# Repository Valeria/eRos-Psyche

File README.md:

# eRos & Psyche
### **Open Source Dildo running on the ESP32 Platform**

V1.0 Attaches to a **ESP32-DevKitC-V4**, **check pinout to make sure it coincides**.

It's meant to drive three (or less) **3.3v motors, max 1A per PWM output**.
Use with Li-Po or Li-Ion **3.7v nominal voltage batteries**.

Connects to a **Blynk.io** server, which can be self-hosted, otherwise, use the free Blynk Cloud server or contact me for a spot on mine.

Mobile app can be recreated by scanning the following QR code on the Blynk phone app:

Hardware files are in the **eRos** directory, meant to be edited on **KiCad v5.0 or higher**.

Firmware files are in the **Psyche** directory, if you open the project on PlatformIO it should load all required Arduino libraries automatically, else, here's a list:

 - shaggydog/OneButton@^1.5.0
 - ayushsharma82/AsyncElegantOTA@^2.2.5
 - ottowinter/AsyncTCP-esphome@^1.2.1
 - ottowinter/ESPAsyncWebServer-esphome@^1.2.7
 - bblanchon/ArduinoJson@^6.17.3
 - s00500/ESPUI@^2.0.0
 - khoih.prog/Blynk_Async_ESP32_BT_WF@^1.2.1
 - adafruit/Adafruit BMP280 Library@^2.4.1
 - teckel12/NewPing@^1.9.1
 - gamegine/HCSR04 ultrasonic sensor@^2.0.2
 - adafruit/Adafruit_VL53L0X@^1.1.1

Firmware.bin must be built with the **huge_app.csv** partition scheme.

Have fun!

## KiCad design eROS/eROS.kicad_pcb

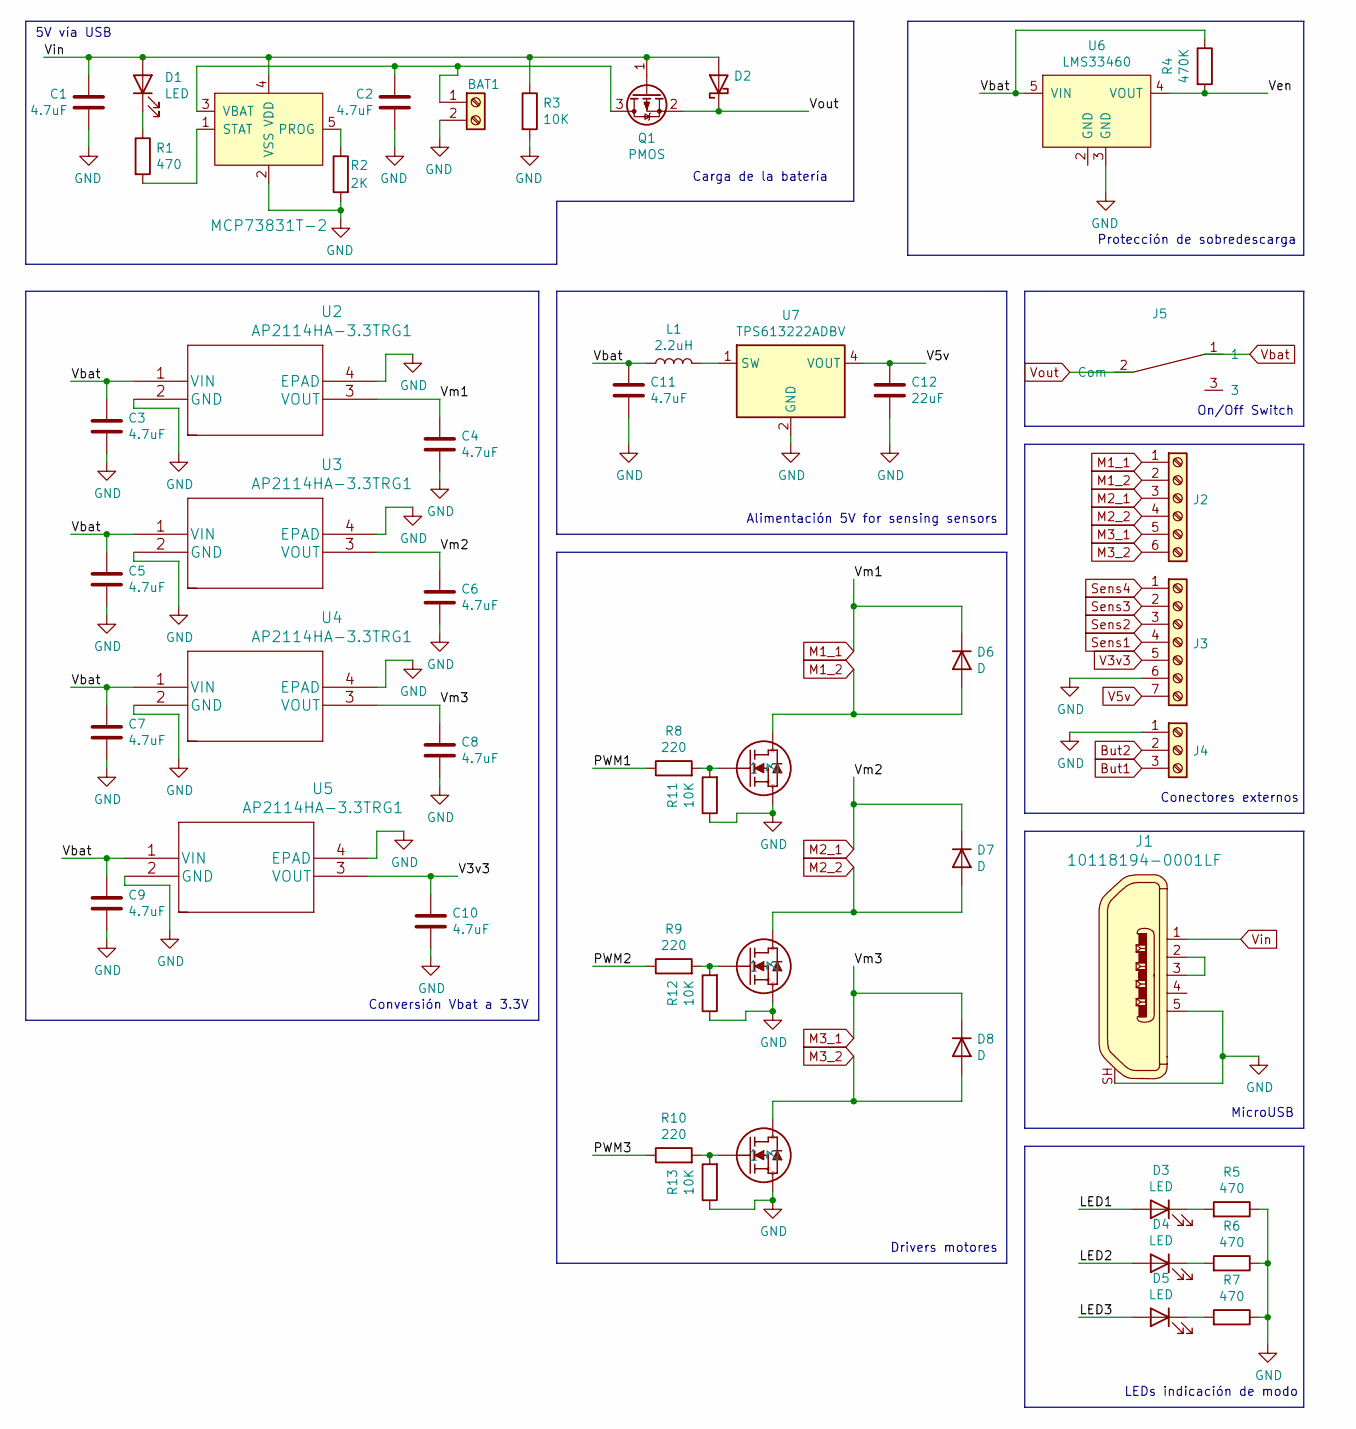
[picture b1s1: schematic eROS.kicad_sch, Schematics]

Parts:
BAT1: Screw_Terminal_01x02; JST_XH_B2B-XH-A_1x02_P2.50mm_Vertical
C1, C2, C3, C4, C5, C6, C7, C8, C9, C10, C11: 4.7uF; C_0805_2012Metric_Pad1.18x1.45mm_HandSolder
C12: 22uF; C_0805_2012Metric_Pad1.18x1.45mm_HandSolder
D1, D3, D4, D5: LED; LED_0805_2012Metric_Pad1.15x1.40mm_HandSolder
D2: D_Schottky; Nexperia_CFP3_SOD-123W_Handsolder
D6, D7, D8: D; Nexperia_CFP3_SOD-123W_Handsolder
J1: 10118194-0001LF; USB_Micro_B_Female_10118194-0001LF_HandSolder; MPN 10118194-0001LF; Digi-Key_PN 609-4618-1-ND
J2: Screw_Terminal_01x06; JST_XH_B6B-XH-A_1x06_P2.50mm_Vertical
J3: Screw_Terminal_01x07; PinHeader_1x07_P2.00mm_Horizontal
J4: Screw_Terminal_01x03; JST_XH_B3B-XH-A_1x03_P2.50mm_Vertical
J5: MiniSlideSwitch; JST_XH_B2B-XH-A_1x02_P2.50mm_Vertical
L1: 2.2uH; L_1008_2520Metric_Pad1.43x2.20mm_HandSolder
MOSFET1, MOSFET2, MOSFET3: IRLML6246TRPBF; SOT-23_Handsoldering
Q1: PMOS; SOT-23_Handsoldering
R1, R5, R6, R7: 470; R_0805_2012Metric_Pad1.20x1.40mm_HandSolder
R2: 2K; R_0805_2012Metric_Pad1.20x1.40mm_HandSolder
R3, R11, R12, R13: 10K; R_0805_2012Metric_Pad1.20x1.40mm_HandSolder
R4: 470K; R_0805_2012Metric_Pad1.20x1.40mm_HandSolder
R8, R9, R10: 220; R_0805_2012Metric_Pad1.20x1.40mm_HandSolder
U1: MCP73831T-2; SOT-23-5_HandSoldering; MPN MCP73831T-2DCI/OT; Digi-Key_PN MCP73831T-2DCI/OTCT-ND
U2, U3, U4, U5: AP2114HA-3.3TRG1; SOT-223-3_TabPin2
U6: LMS33460; SOT-353_SC-70-5_Handsoldering; mpn LMS33460
U7: TPS613222ADBV; SOT-23-5_HandSoldering

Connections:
/LED1: D3.2 (A)
/LED2: D4.2 (A)
/LED3: D5.2 (A)
/PWM1: R8.1
/PWM2: R9.1
/PWM3: R10.1
/Ven: R4.2, U6.4 (VOUT)
But1: J4.3
But2: J4.2
GND: BAT1.2, C1.2, C2.2, C3.2, C4.2, C5.2, C6.2, C7.2, C8.2, C9.2, C10.2, C11.2, C12.2, J1.5, J1.SH, J3.6, J4.1, MOSFET1.2, MOSFET2.2, MOSFET3.2, R2.2, R3.2, R5.1, R6.1, R7.1, R11.1, R12.1, R13.1, U1.2 (VSS), U2.2 (GND), U2.4 (EPAD), U3.2 (GND), U3.4 (EPAD), U4.2 (GND), U4.4 (EPAD), U5.2 (GND), U5.4 (EPAD), U6.3 (GND), U7.2 (GND)
M1_1: C4.1, D6.1 (K), J2.1, U2.3 (VOUT)
M1_2: D6.2 (A), J2.2, MOSFET1.3
M2_1: C6.1, D7.1 (K), J2.3, U3.3 (VOUT)
M2_2: D7.2 (A), J2.4, MOSFET2.3
M3_1: C8.1, D8.1 (K), J2.5, U4.3 (VOUT)
M3_2: D8.2 (A), J2.6, MOSFET3.3
unnamed: BAT1.1, C2.1, Q1.3 (D), U1.3 (VBAT)
unnamed: D1.1 (K), R1.1
unnamed: D3.1 (K), R5.2
unnamed: D4.1 (K), R6.2
unnamed: D5.1 (K), R7.2
unnamed: J1.2, J1.3
unnamed: L1.2, U7.1 (SW)
unnamed: MOSFET1.1, R8.2, R11.2
unnamed: MOSFET2.1, R9.2, R12.2
unnamed: MOSFET3.1, R10.2, R13.2
unnamed: R1.2, U1.1 (STAT)
unnamed: R2.1, U1.5 (PROG)
Sens1: J3.4
Sens2: J3.3
Sens3: J3.2
Sens4: J3.1
V3v3: C10.1, J3.5, U5.3 (VOUT)
V5v: C12.1, J3.7, U7.4 (VOUT)
Vbat: C3.1, C5.1, C7.1, C9.1, C11.1, J5.1, L1.1, R4.1, U2.1 (VIN), U3.1 (VIN), U4.1 (VIN), U5.1 (VIN), U6.5 (VIN)
Vin: C1.1, D1.2 (A), D2.2 (A), J1.1, Q1.1 (G), R3.1, U1.4 (VDD)
Vout: D2.1 (K), J5.2 (Com), Q1.2 (S)

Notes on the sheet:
5V vía USB
Conversión Vbat a 3.3V
Carga de la batería
Alimentación 5V for sensing sensors
Drivers motores
Protección de sobredescarga
LEDs indicación de modo
Conectores externos
On/Off Switch
MicroUSB

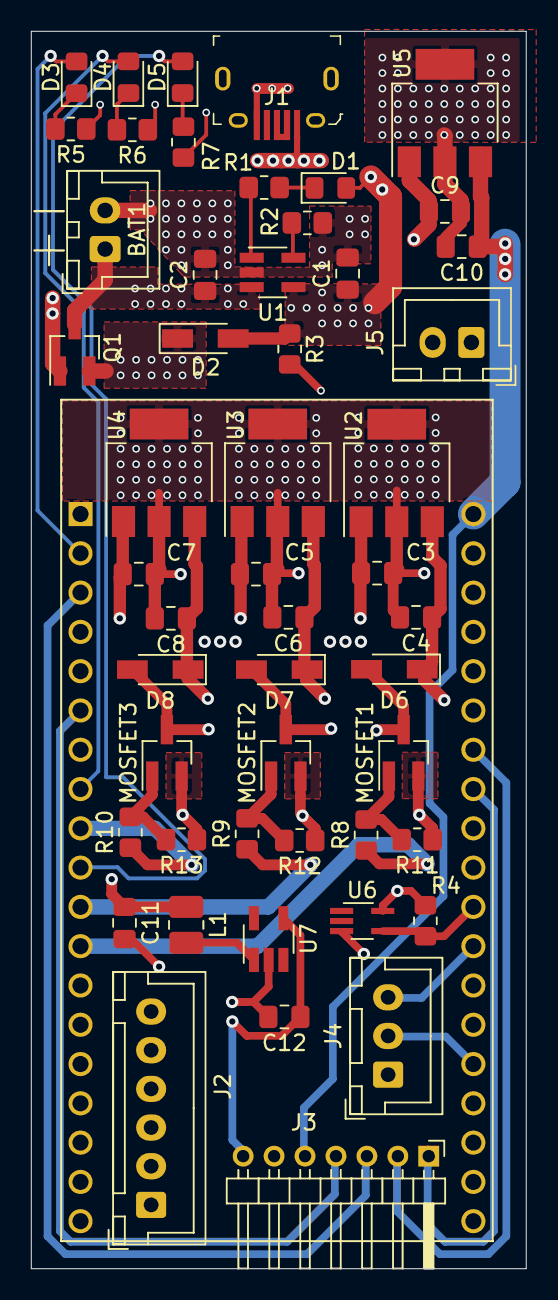
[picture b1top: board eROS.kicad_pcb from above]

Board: 4 copper layers, 32.0 x 80.0 mm, 51 parts (0 on the bottom side), 25 nets.

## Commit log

2021-10-20 KiCad Hardware files added
2021-10-20 Schematics/PCB images
2021-10-20 PlatformIO (or Arduino editor) Firmware files
2021-10-20 App images + Blank project copy QR
2021-10-20 PCB 3D Render
2021-10-20 Rename LICENSE to LICENSE-SOFTWARE
2021-10-20 Add Licenses Info Image
2021-10-20 Add Hardware LICENSE
